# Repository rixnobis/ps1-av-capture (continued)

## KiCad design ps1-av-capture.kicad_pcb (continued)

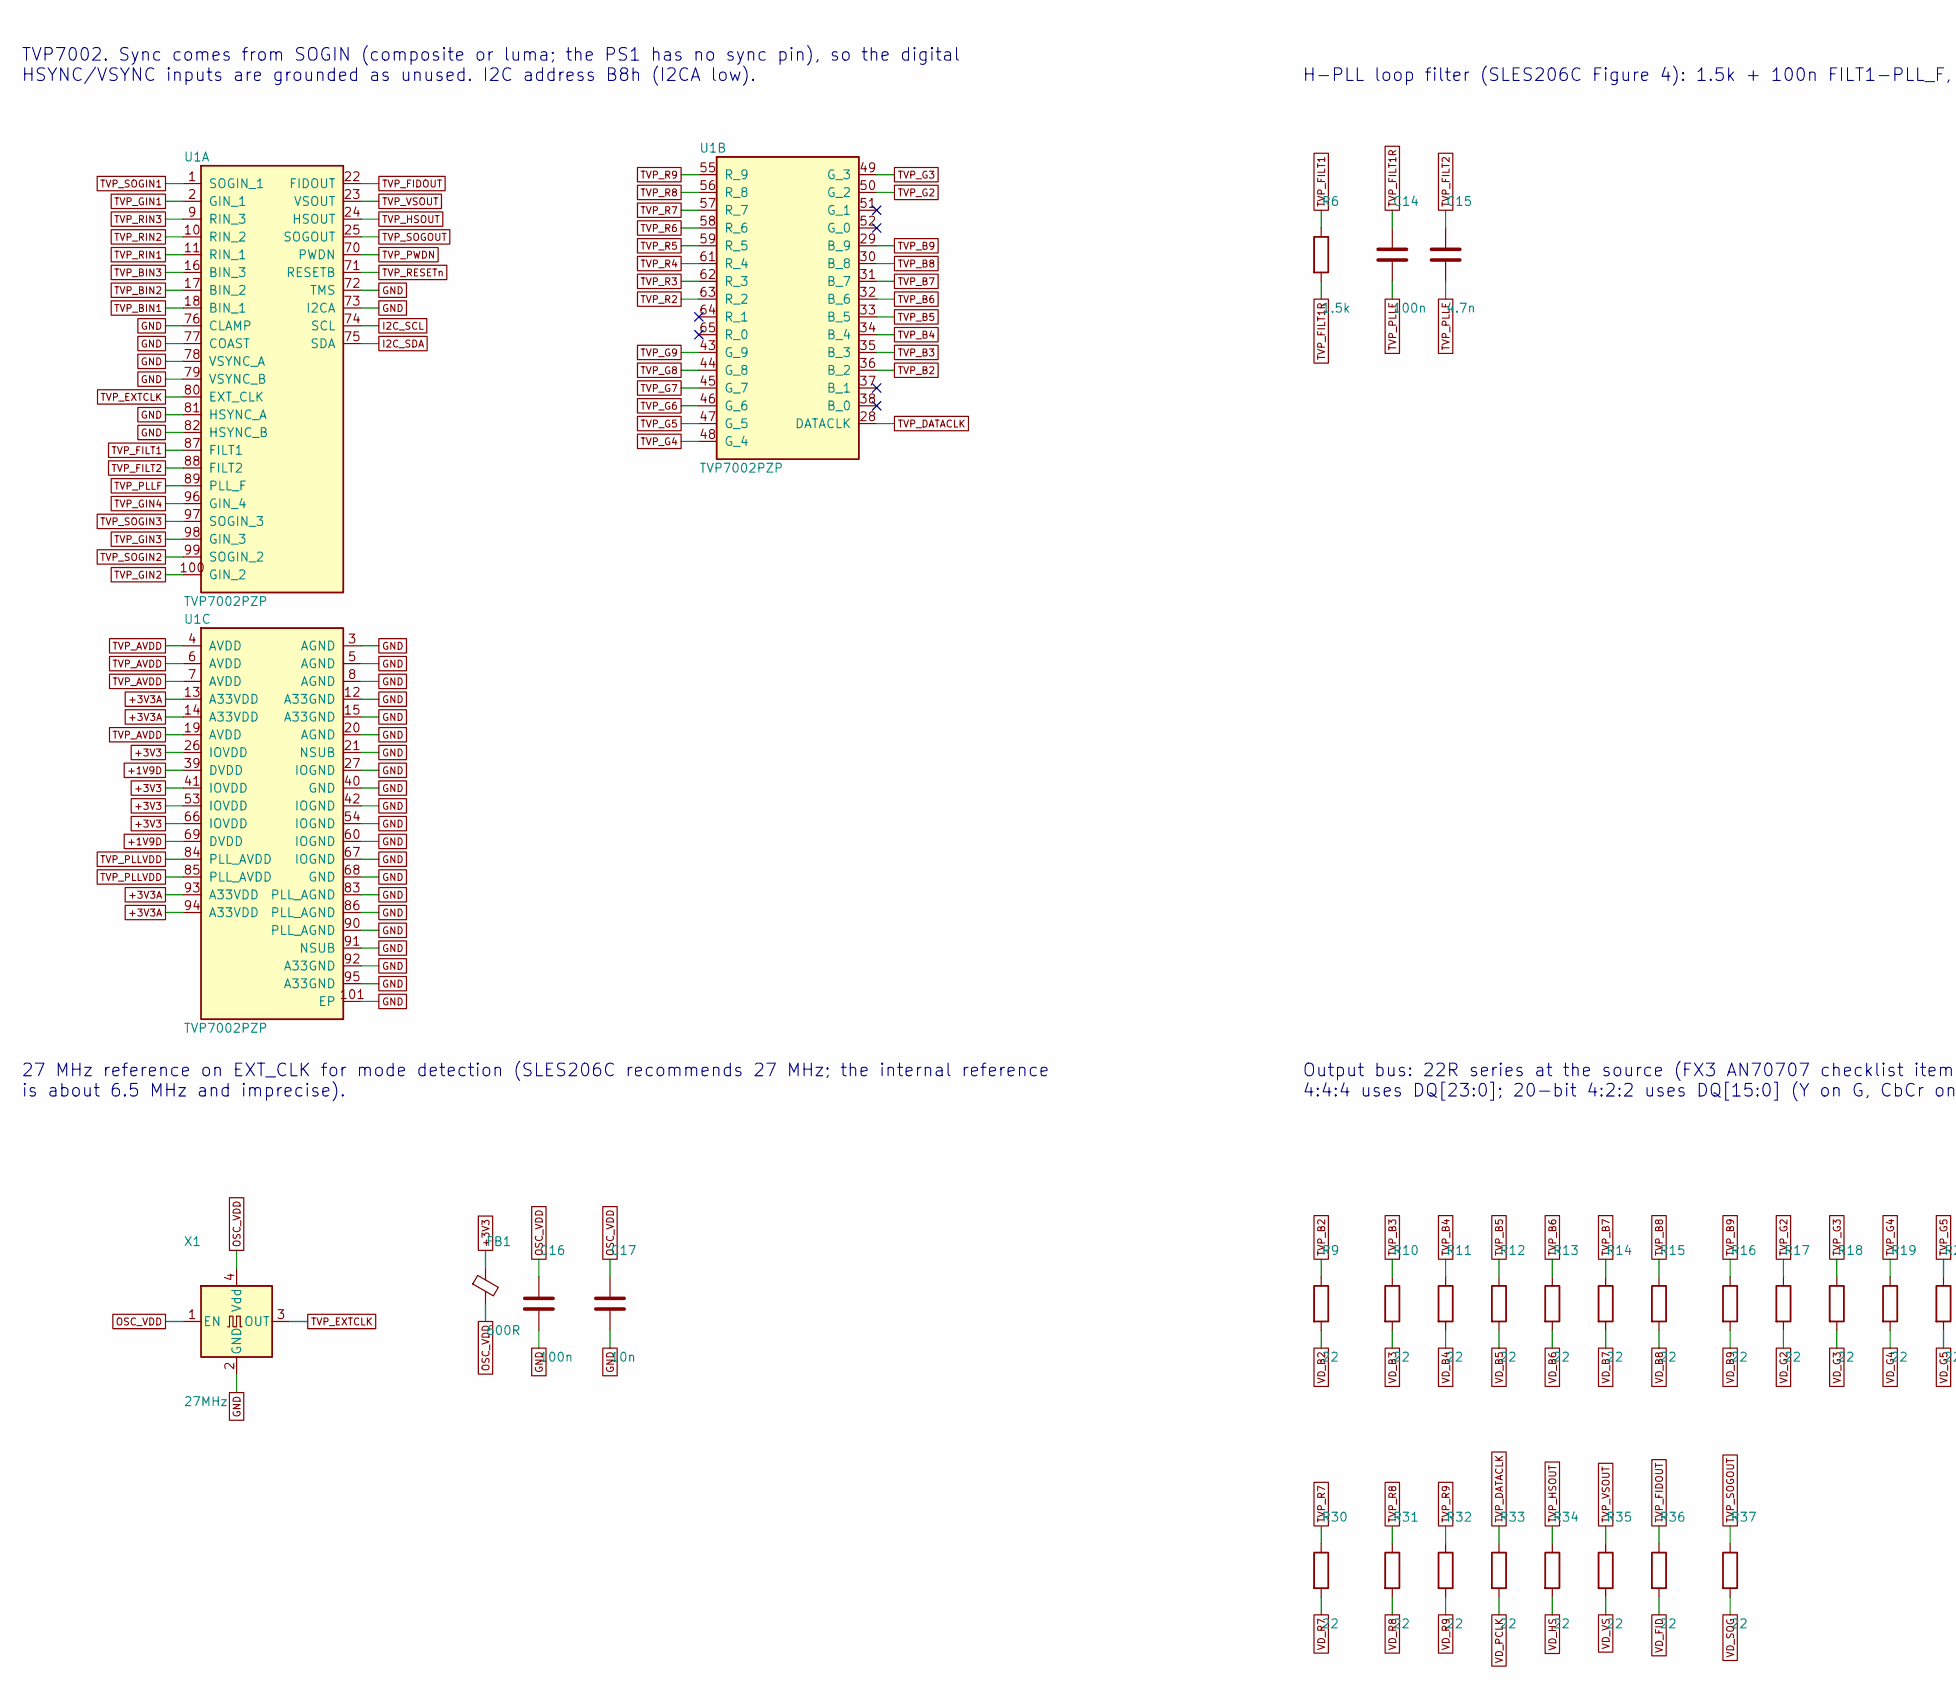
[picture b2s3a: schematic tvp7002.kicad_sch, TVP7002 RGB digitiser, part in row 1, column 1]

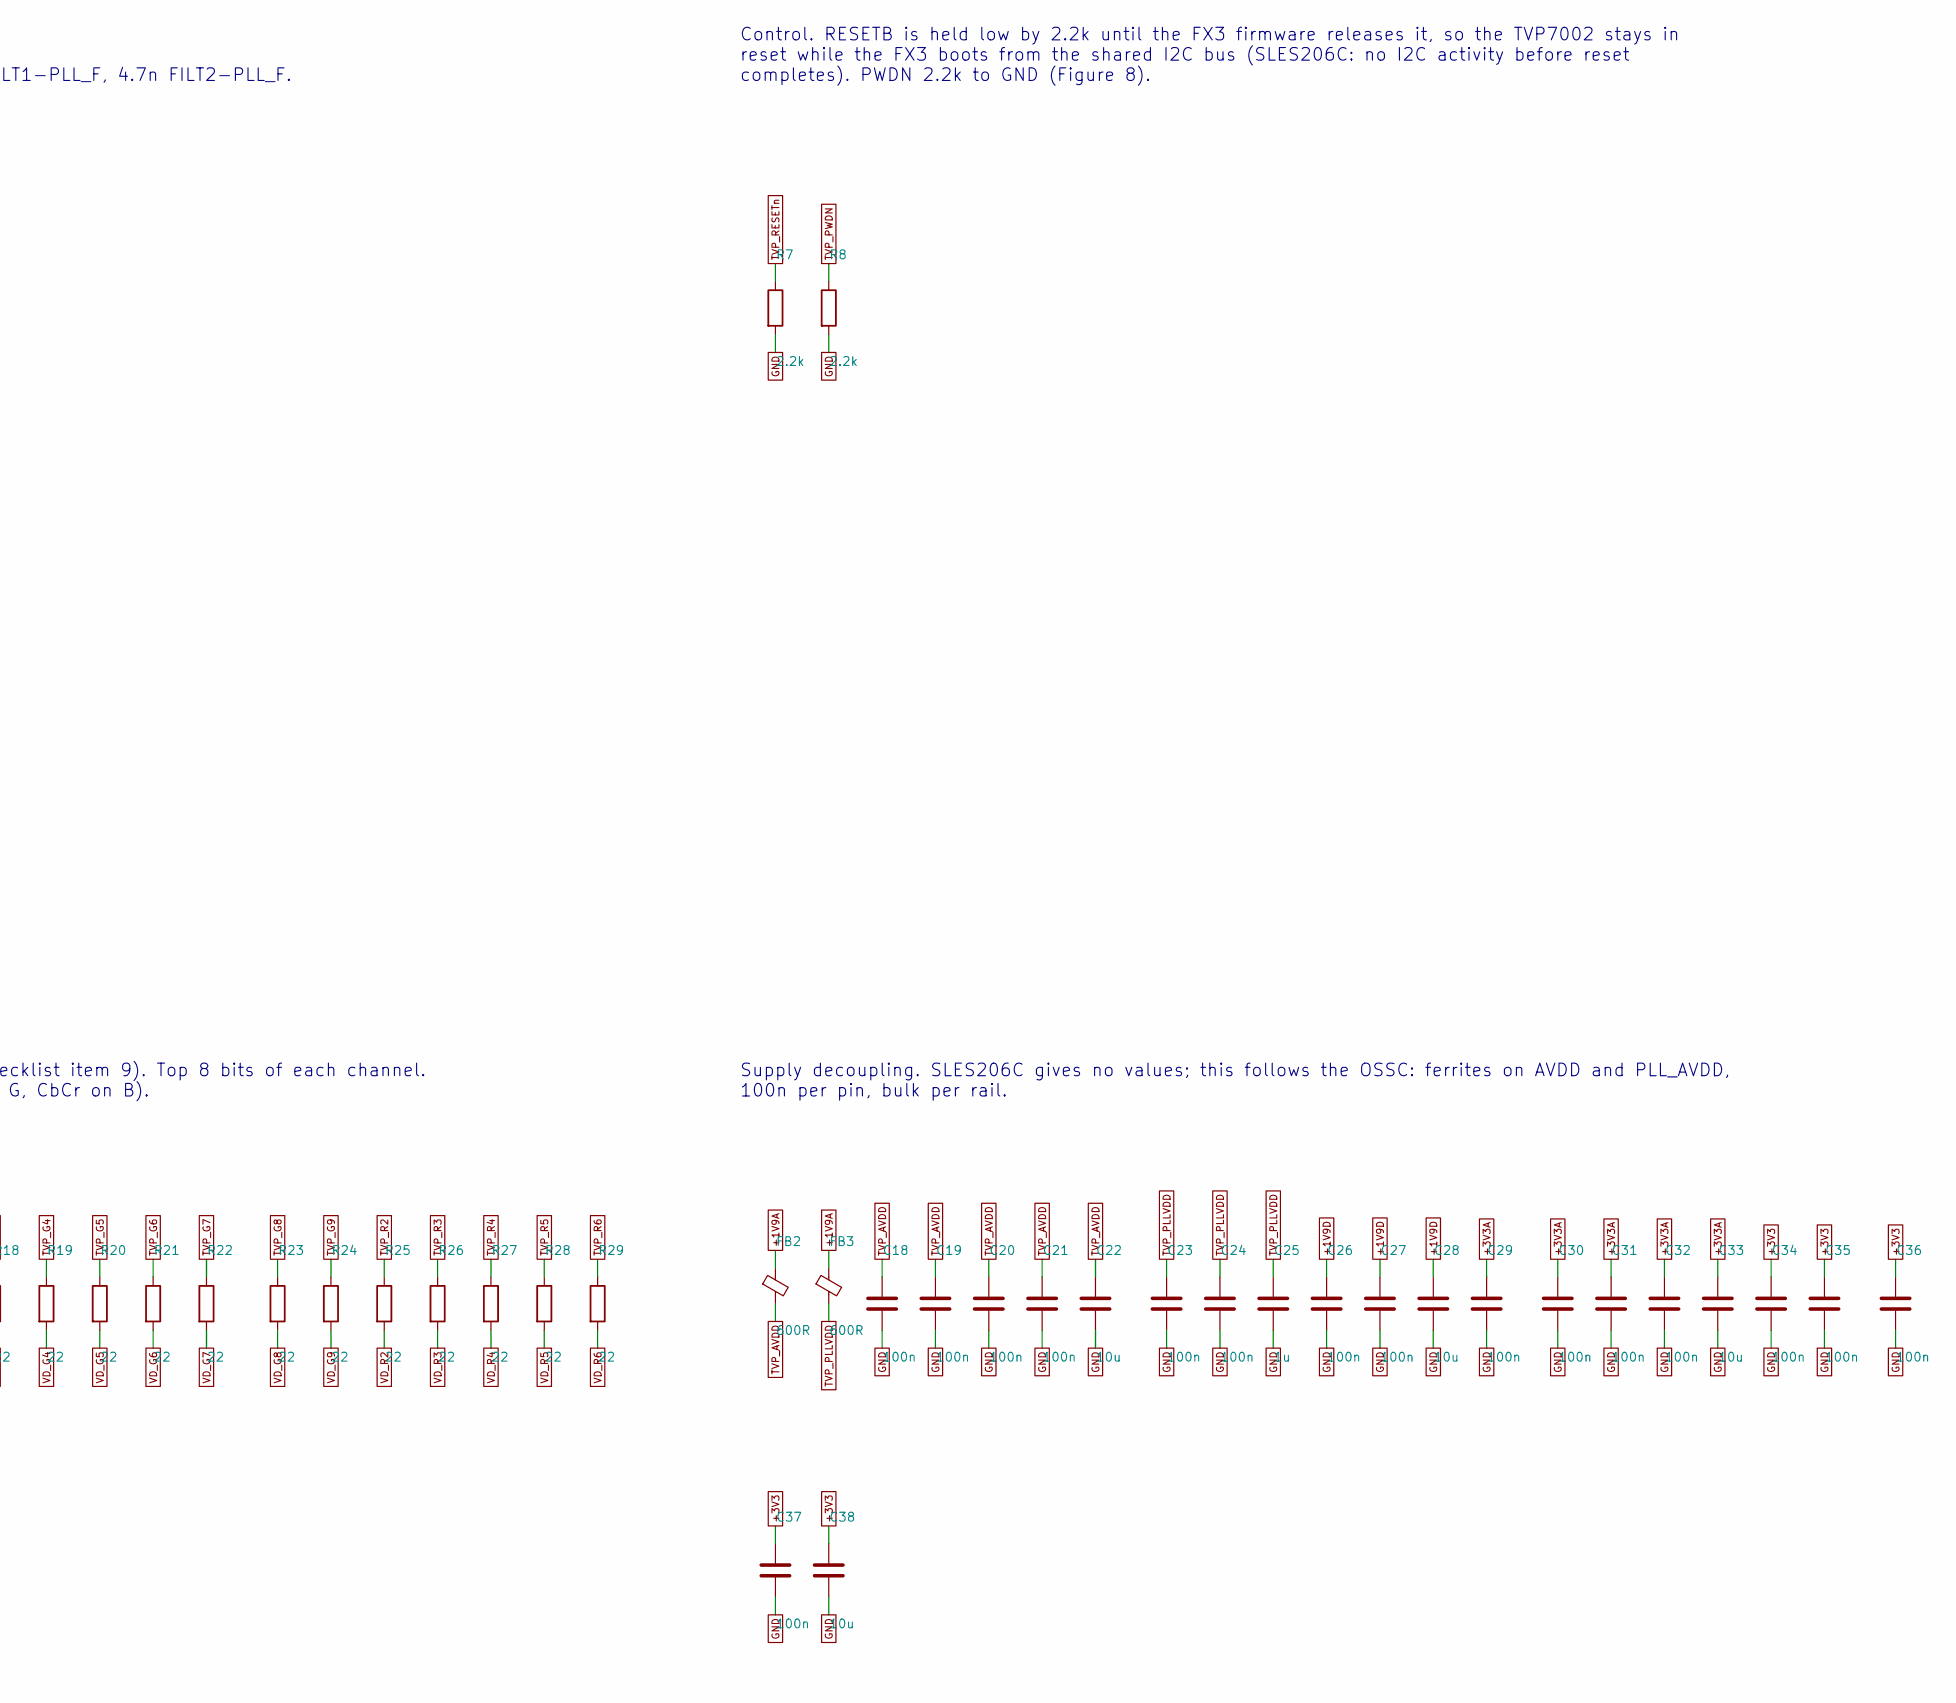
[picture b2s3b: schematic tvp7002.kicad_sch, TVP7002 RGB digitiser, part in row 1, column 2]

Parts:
C14, C16, C18, C19, C20, C21, C23, C24, C26, C27, C29, C30, C31, C32, C34, C35, C36, C37: 100n; C_0402_1005Metric; LCSC C1525
C15: 4.7n; C_0402_1005Metric; LCSC C1538
C17: 10n; C_0402_1005Metric; LCSC C15195
C22, C28, C33, C38: 10u; C_0603_1608Metric; LCSC C19702
C25: 1u; C_0402_1005Metric; LCSC C52923
FB1, FB2, FB3: 600R; L_0603_1608Metric; LCSC C108301
R6: 1.5k; R_0402_1005Metric; LCSC C25867
R7, R8: 2.2k; R_0402_1005Metric; LCSC C25879
R9, R10, R11, R12, R13, R14, R15, R16, R17, R18, R19, R20, R21, R22, R23, R24, R25, R26, R27, R28, R29, R30, R31, R32, R33, R34, R35, R36, R37: 22; R_0402_1005Metric; LCSC C25092
U1: TVP7002PZP; HTQFP-100_L14.0-W14.0-P0.50-LS16.0-BL-EP6.2; LCSC C3824085
X1: 27MHz; Oscillator_SMD_Abracon_ASE-4Pin_3.2x2.5mm; LCSC C725995

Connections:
+1V9A: FB2.1, FB3.1; also elsewhere on the board
+1V9D: C26.1, C27.1, C28.1, U1.39 (DVDD), U1.69 (DVDD); also elsewhere on the board
+3V3: C34.1, C35.1, C36.1, C37.1, C38.1, FB1.1, U1.26 (IOVDD), U1.41 (IOVDD), U1.53 (IOVDD), U1.66 (IOVDD); also elsewhere on the board
+3V3A: C29.1, C30.1, C31.1, C32.1, C33.1, U1.13 (A33VDD), U1.14 (A33VDD), U1.93 (A33VDD), U1.94 (A33VDD); also elsewhere on the board
GND: C16.2, C17.2, C18.2, C19.2, C20.2, C21.2, C22.2, C23.2, C24.2, C25.2, C26.2, C27.2, C28.2, C29.2, C30.2, C31.2, C32.2, C33.2, C34.2, C35.2, C36.2, C37.2, C38.2, R7.2, R8.2, U1.3 (AGND), U1.5 (AGND), U1.8 (AGND), U1.12 (A33GND), U1.15 (A33GND), U1.20 (AGND), U1.21 (NSUB), U1.27 (IOGND), U1.40 (GND), U1.42 (IOGND), U1.54 (IOGND), U1.60 (IOGND), U1.67 (IOGND), U1.68 (GND), U1.72 (TMS), U1.73 (I2CA), U1.76 (CLAMP), U1.77 (COAST), U1.78 (VSYNC_A), U1.79 (VSYNC_B), U1.81 (HSYNC_A), U1.82 (HSYNC_B), U1.83 (PLL_AGND), U1.86 (PLL_AGND), U1.90 (PLL_AGND), U1.91 (NSUB), U1.92 (A33GND), U1.95 (A33GND), U1.101 (EP), X1.2 (GND); also elsewhere on the board
I2C_SCL: U1.74 (SCL); also elsewhere on the board
I2C_SDA: U1.75 (SDA); also elsewhere on the board
OSC_VDD: C16.1, C17.1, FB1.2, X1.1 (EN), X1.4 (Vdd)
TVP_AVDD: C18.1, C19.1, C20.1, C21.1, C22.1, FB2.2, U1.4 (AVDD), U1.6 (AVDD), U1.7 (AVDD), U1.19 (AVDD)
TVP_B2: R9.1, U1.36 (B_2)
TVP_B3: R10.1, U1.35 (B_3)
TVP_B4: R11.1, U1.34 (B_4)
TVP_B5: R12.1, U1.33 (B_5)
TVP_B6: R13.1, U1.32 (B_6)
TVP_B7: R14.1, U1.31 (B_7)
TVP_B8: R15.1, U1.30 (B_8)
TVP_B9: R16.1, U1.29 (B_9)
TVP_BIN1: U1.18 (BIN_1); also elsewhere on the board
TVP_BIN2: U1.17 (BIN_2); also elsewhere on the board
TVP_BIN3: U1.16 (BIN_3); also elsewhere on the board
TVP_DATACLK: R33.1, U1.28 (DATACLK)
TVP_EXTCLK: U1.80 (EXT_CLK), X1.3 (OUT)
TVP_FIDOUT: R36.1, U1.22 (FIDOUT)
TVP_FILT1: R6.1, U1.87 (FILT1)
TVP_FILT1R: C14.1, R6.2
TVP_FILT2: C15.1, U1.88 (FILT2)
TVP_G2: R17.1, U1.50 (G_2)
TVP_G3: R18.1, U1.49 (G_3)
TVP_G4: R19.1, U1.48 (G_4)
TVP_G5: R20.1, U1.47 (G_5)
TVP_G6: R21.1, U1.46 (G_6)
TVP_G7: R22.1, U1.45 (G_7)
TVP_G8: R23.1, U1.44 (G_8)
TVP_G9: R24.1, U1.43 (G_9)
TVP_GIN1: U1.2 (GIN_1); also elsewhere on the board
TVP_GIN2: U1.100 (GIN_2); also elsewhere on the board
TVP_GIN3: U1.98 (GIN_3); also elsewhere on the board
TVP_GIN4: U1.96 (GIN_4); also elsewhere on the board
TVP_HSOUT: R34.1, U1.24 (HSOUT)
TVP_PLLF: C14.2, C15.2, U1.89 (PLL_F)
TVP_PLLVDD: C23.1, C24.1, C25.1, FB3.2, U1.84 (PLL_AVDD), U1.85 (PLL_AVDD)
TVP_PWDN: R8.1, U1.70 (PWDN)
TVP_R2: R25.1, U1.63 (R_2)
TVP_R3: R26.1, U1.62 (R_3)
TVP_R4: R27.1, U1.61 (R_4)
TVP_R5: R28.1, U1.59 (R_5)
TVP_R6: R29.1, U1.58 (R_6)
TVP_R7: R30.1, U1.57 (R_7)
TVP_R8: R31.1, U1.56 (R_8)
TVP_R9: R32.1, U1.55 (R_9)
TVP_RESETn: R7.1, U1.71 (RESETB); also elsewhere on the board
TVP_RIN1: U1.11 (RIN_1); also elsewhere on the board
TVP_RIN2: U1.10 (RIN_2); also elsewhere on the board
TVP_RIN3: U1.9 (RIN_3); also elsewhere on the board
TVP_SOGIN1: U1.1 (SOGIN_1); also elsewhere on the board
TVP_SOGIN2: U1.99 (SOGIN_2); also elsewhere on the board
TVP_SOGIN3: U1.97 (SOGIN_3); also elsewhere on the board
TVP_SOGOUT: R37.1, U1.25 (SOGOUT)
TVP_VSOUT: R35.1, U1.23 (VSOUT)
VD_B2: R9.2; also elsewhere on the board
VD_B3: R10.2; also elsewhere on the board
VD_B4: R11.2; also elsewhere on the board
VD_B5: R12.2; also elsewhere on the board
VD_B6: R13.2; also elsewhere on the board
VD_B7: R14.2; also elsewhere on the board
VD_B8: R15.2; also elsewhere on the board
VD_B9: R16.2; also elsewhere on the board
VD_FID: R36.2; also elsewhere on the board
VD_G2: R17.2; also elsewhere on the board
VD_G3: R18.2; also elsewhere on the board
VD_G4: R19.2; also elsewhere on the board
VD_G5: R20.2; also elsewhere on the board
VD_G6: R21.2; also elsewhere on the board
VD_G7: R22.2; also elsewhere on the board
VD_G8: R23.2; also elsewhere on the board
VD_G9: R24.2; also elsewhere on the board
VD_HS: R34.2; also elsewhere on the board
VD_PCLK: R33.2; also elsewhere on the board
VD_R2: R25.2; also elsewhere on the board
VD_R3: R26.2; also elsewhere on the board
VD_R4: R27.2; also elsewhere on the board
VD_R5: R28.2; also elsewhere on the board
VD_R6: R29.2; also elsewhere on the board
VD_R7: R30.2; also elsewhere on the board
VD_R8: R31.2; also elsewhere on the board
VD_R9: R32.2; also elsewhere on the board
VD_SOG: R37.2; also elsewhere on the board
VD_VS: R35.2; also elsewhere on the board

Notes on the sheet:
TVP7002. Sync comes from SOGIN (composite or luma; the PS1 has no sync pin), so the digital HSYNC/VSYNC inputs are grounded as unused. I2C address B8h (I2CA low).
H-PLL loop filter (SLES206C Figure 4): 1.5k + 100n FILT1-PLL_F, 4.7n FILT2-PLL_F.
Control. RESETB is held low by 2.2k until the FX3 firmware releases it, so the TVP7002 stays in reset while the FX3 boots from the shared I2C bus (SLES206C: no I2C activity before reset completes). PWDN 2.2k to GND (Figure 8).
27 MHz reference on EXT_CLK for mode detection (SLES206C recommends 27 MHz; the internal reference is about 6.5 MHz and imprecise).
Output bus: 22R series at the source (FX3 AN70707 checklist item 9). Top 8 bits of each channel. 4:4:4 uses DQ[23:0]; 20-bit 4:2:2 uses DQ[15:0] (Y on G, CbCr on B).
Supply decoupling. SLES206C gives no values; this follows the OSSC: ferrites on AVDD and PLL_AVDD, 100n per pin, bulk per rail.

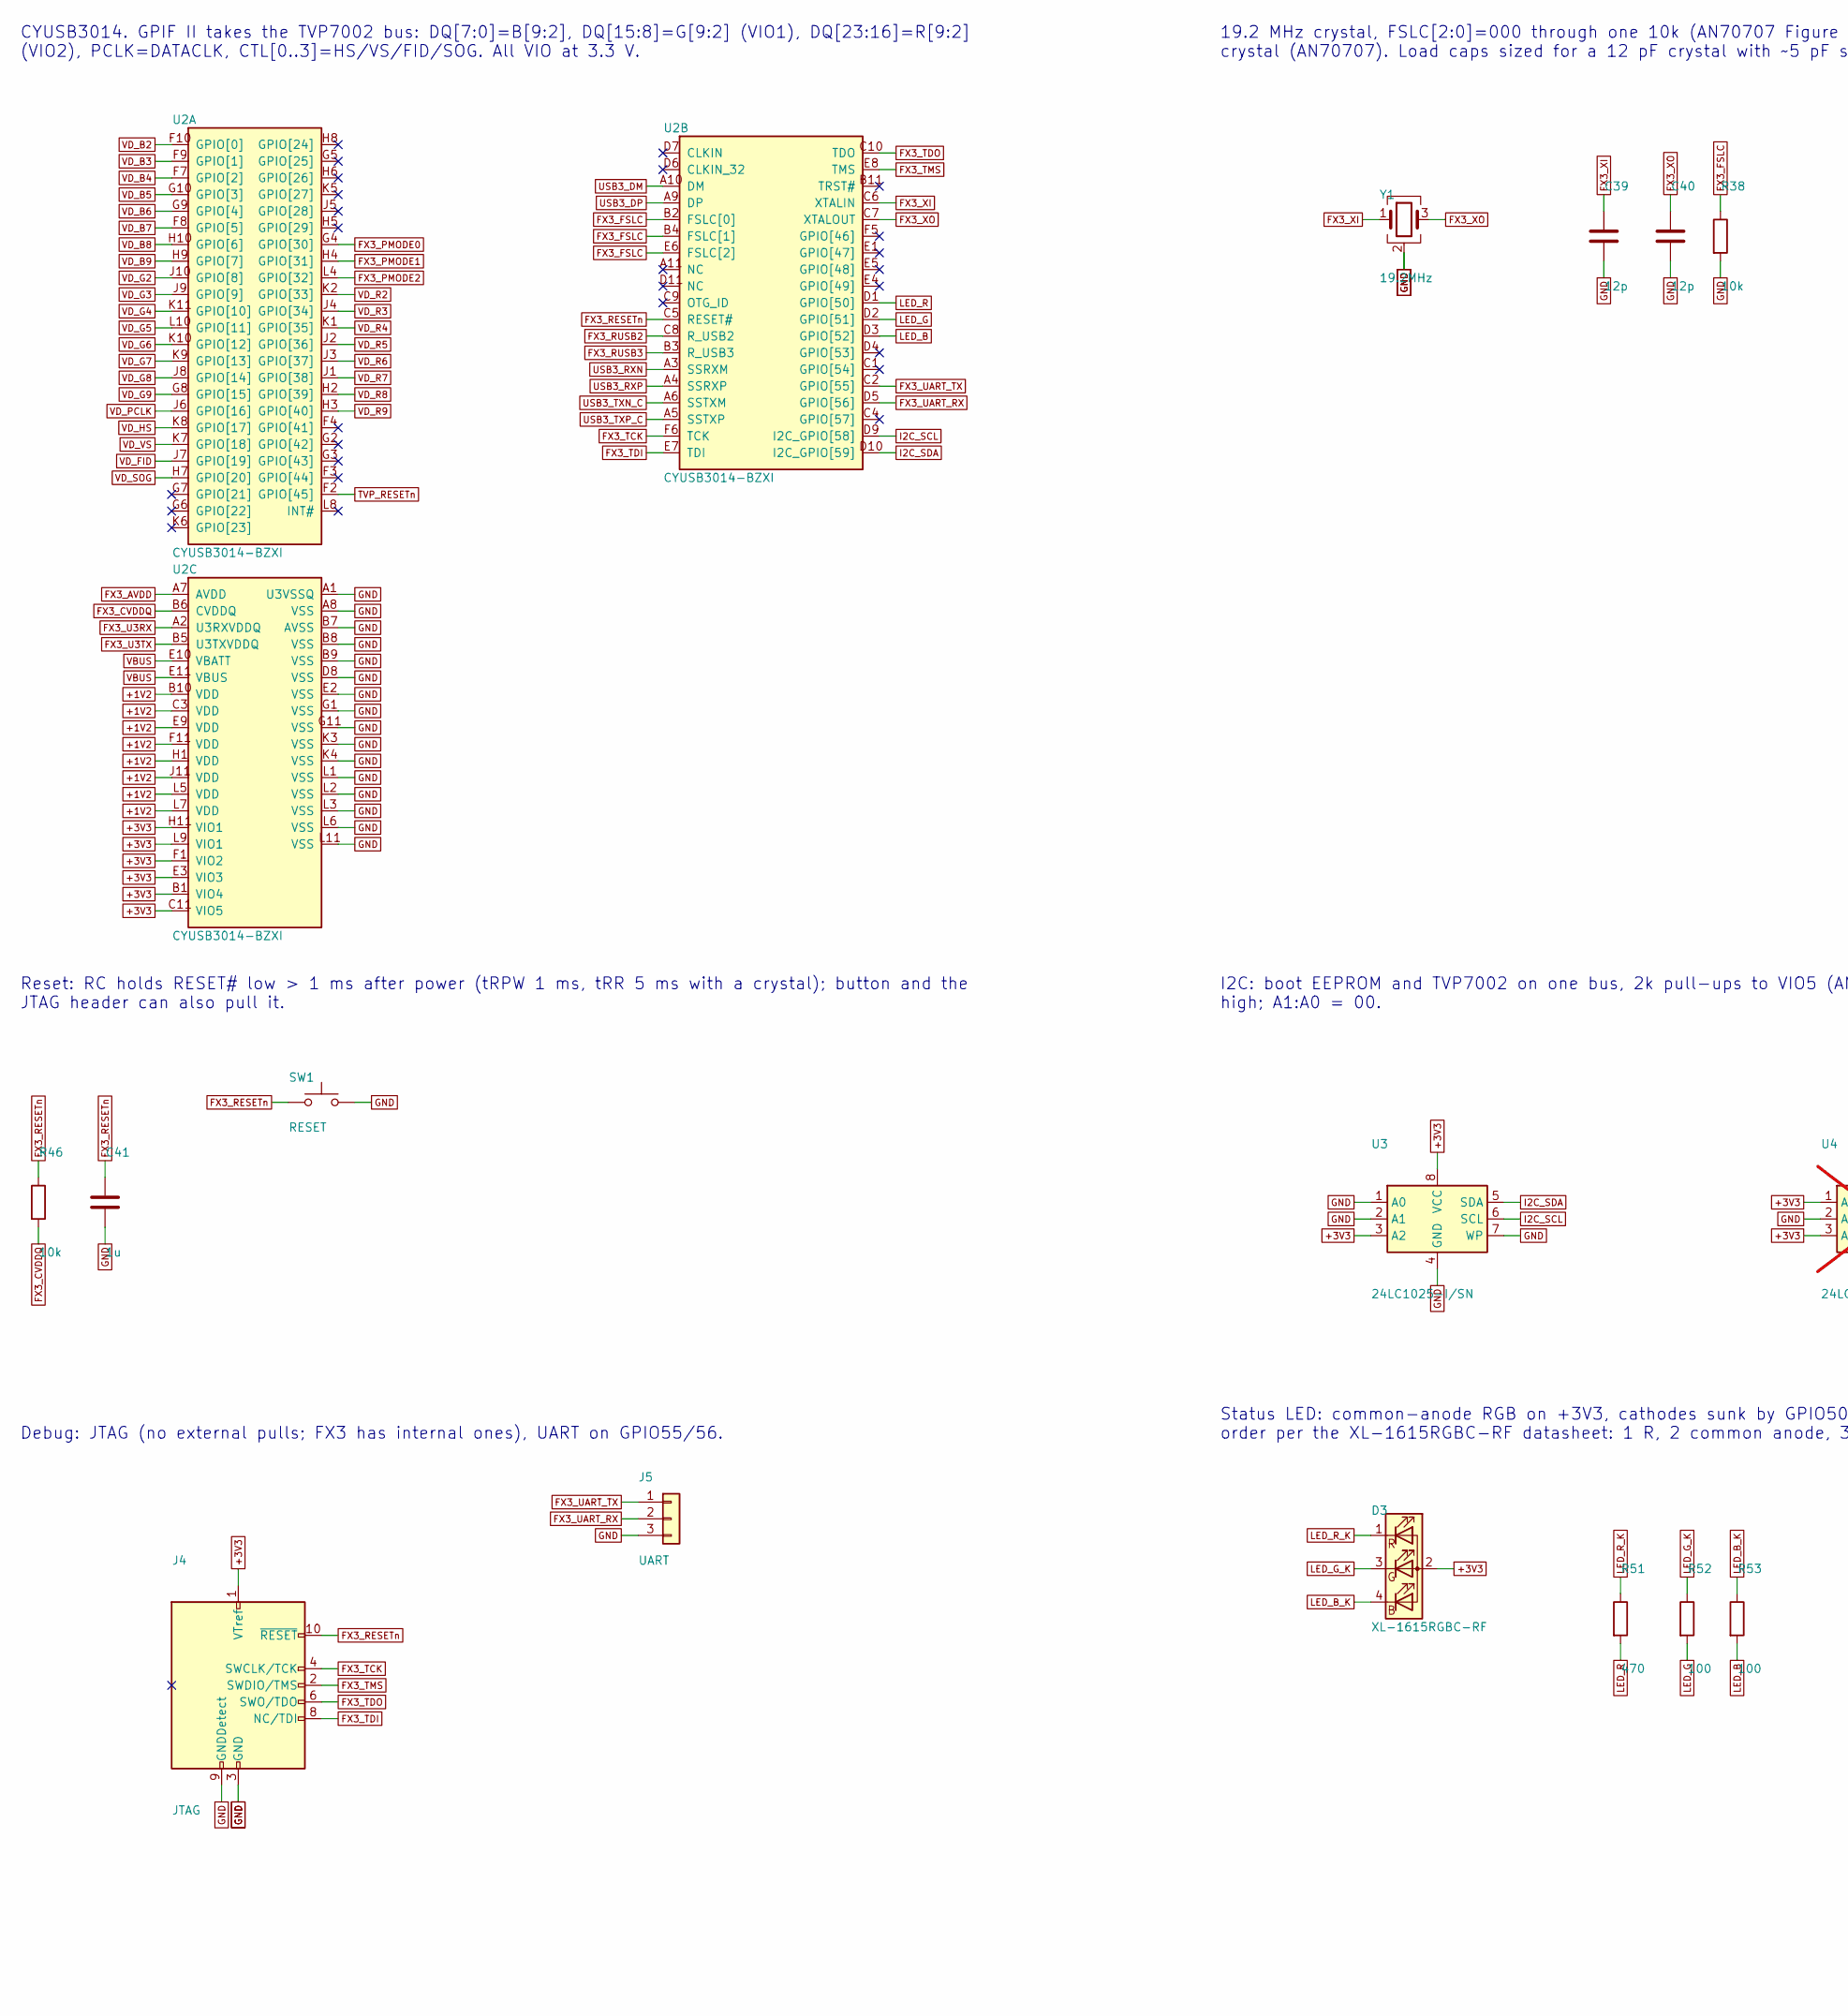
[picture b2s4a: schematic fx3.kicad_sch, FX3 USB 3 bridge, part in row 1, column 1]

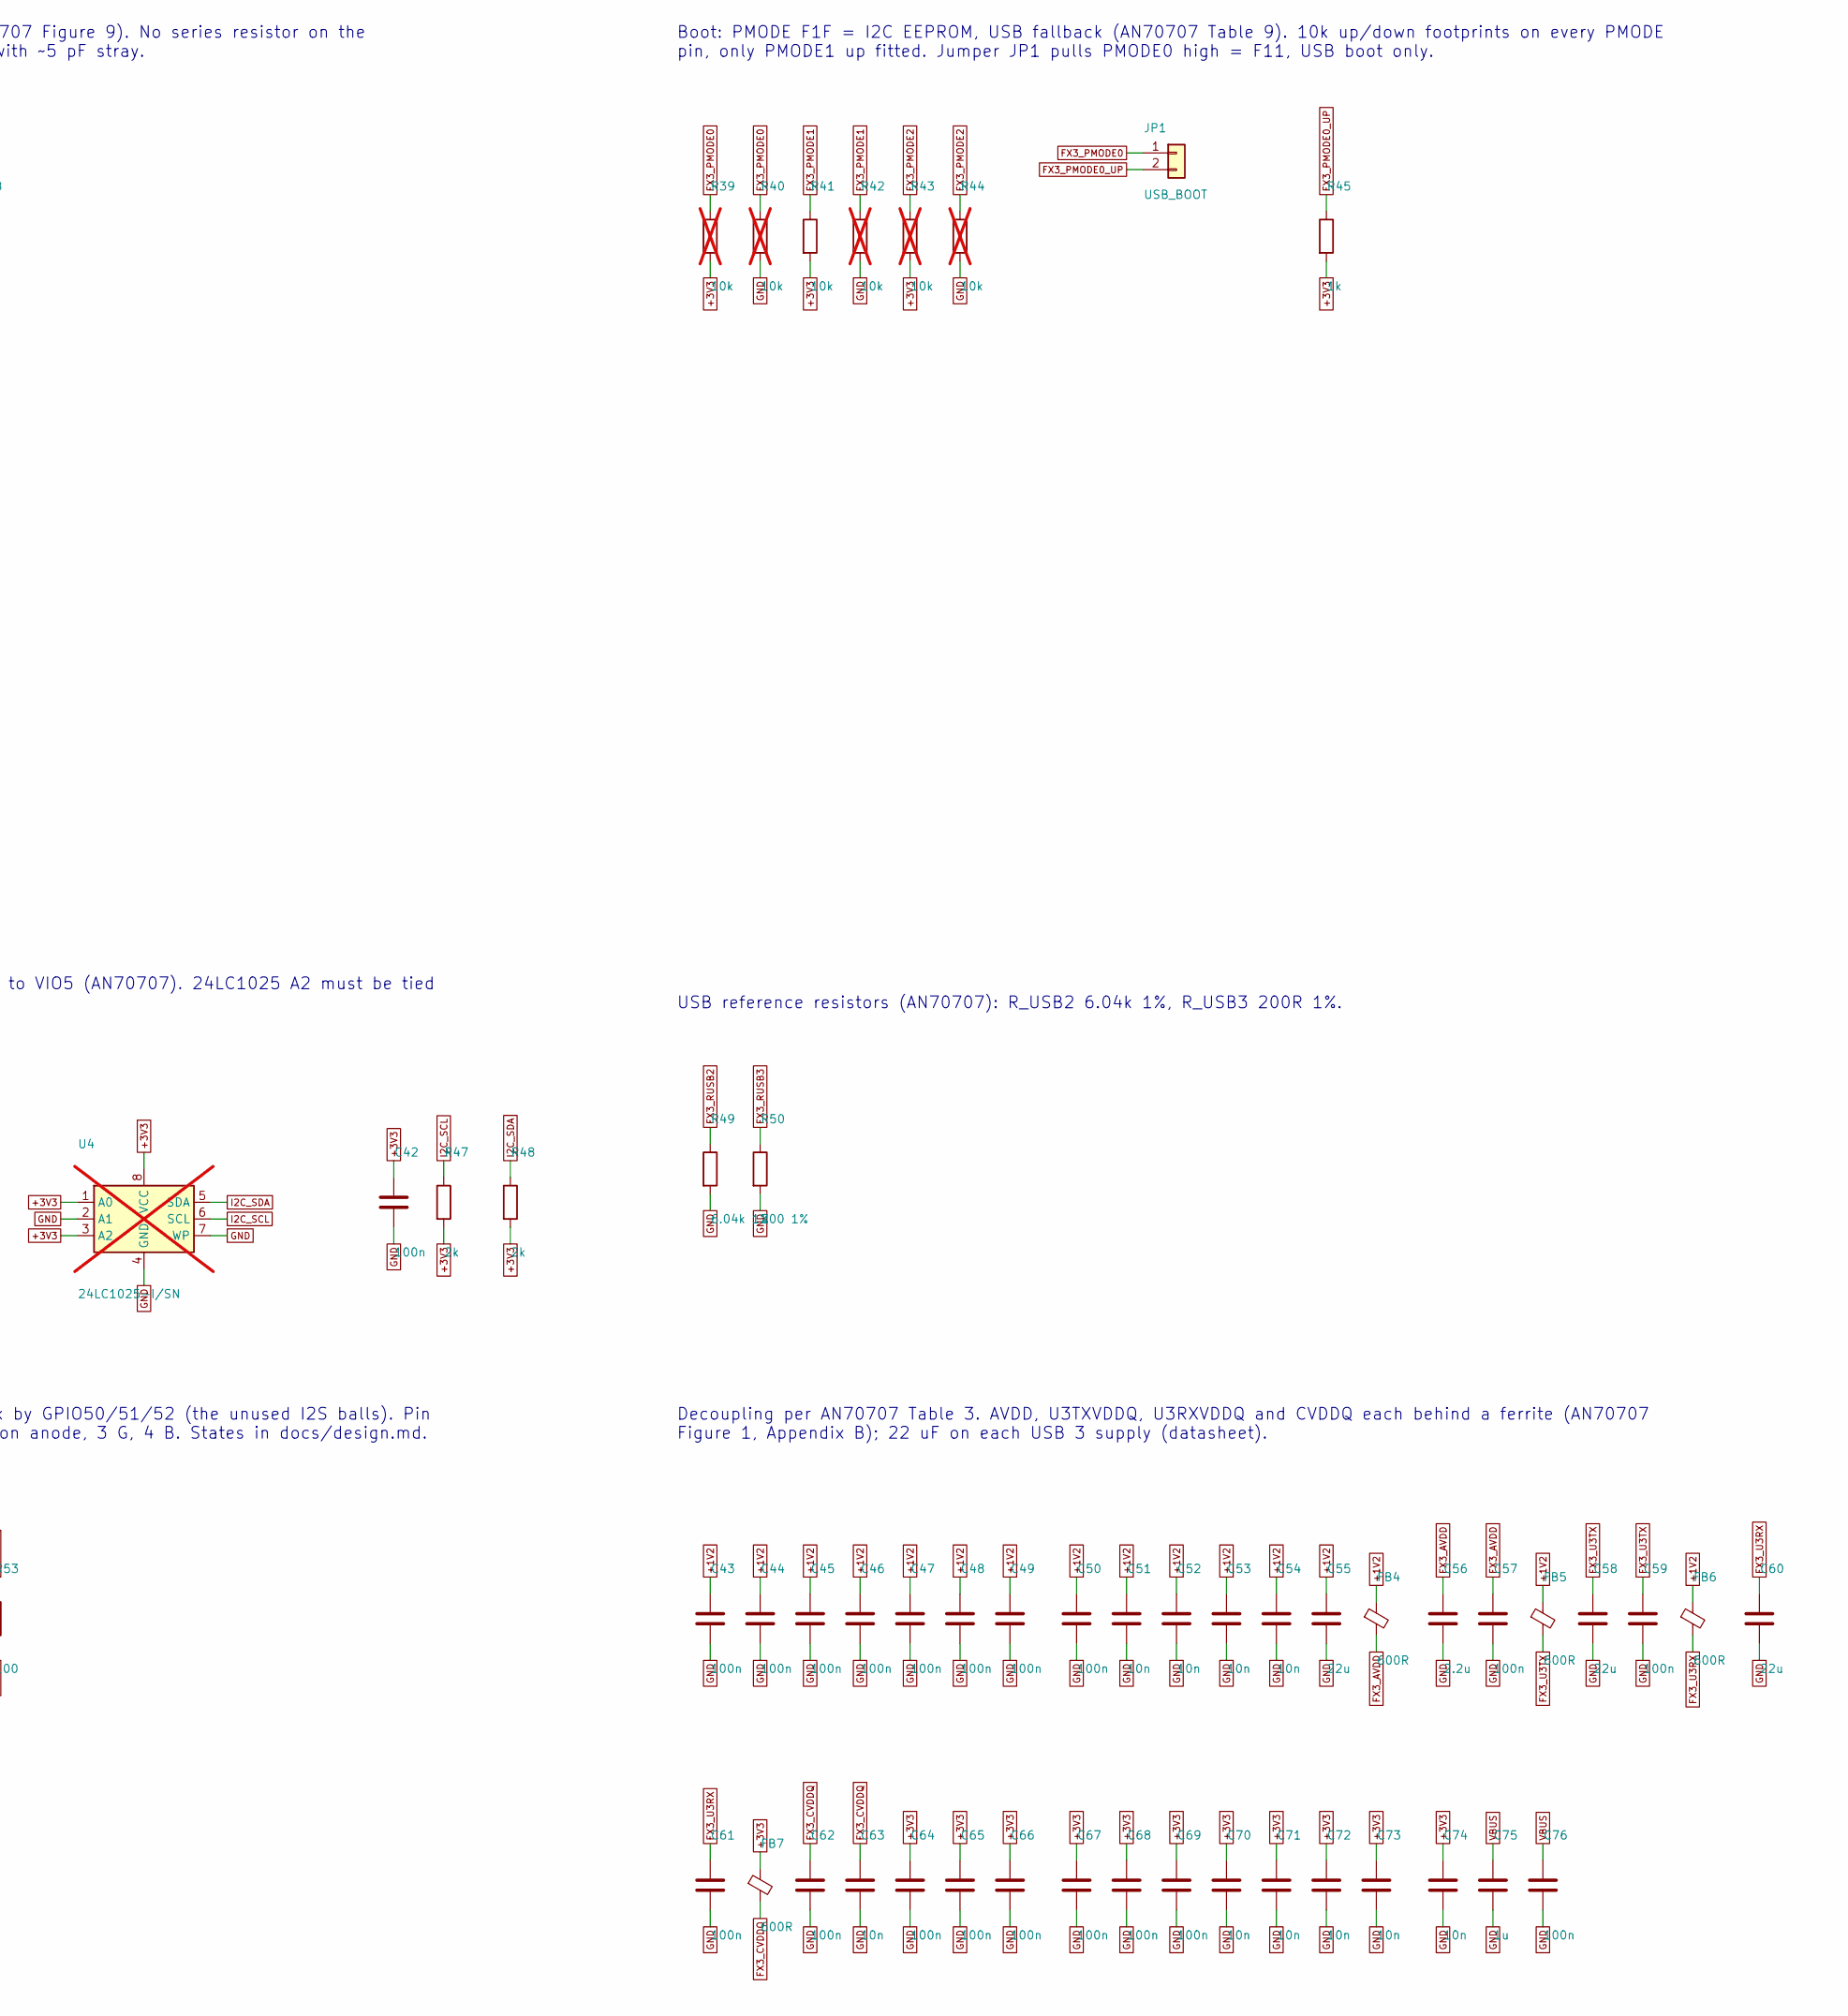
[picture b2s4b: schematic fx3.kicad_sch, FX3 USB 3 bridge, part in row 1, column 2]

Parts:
C39, C40: 12p; C_0402_1005Metric; LCSC C1547
C41, C75: 1u; C_0402_1005Metric; LCSC C52923
C42, C43, C44, C45, C46, C47, C48, C49, C50, C57, C59, C61, C62, C64, C65, C66, C67, C68, C69, C76: 100n; C_0402_1005Metric; LCSC C1525
C51, C52, C53, C54, C63, C70, C71, C72, C73, C74: 10n; C_0402_1005Metric; LCSC C15195
C55, C58, C60: 22u; C_0805_2012Metric; LCSC C45783
C56: 2.2u; C_0603_1608Metric; LCSC C23630
D3: XL-1615RGBC-RF; LED-ARRAY-SMD_4P-L1.6-W1.5-BR_XL-1615RGBC-RF; LCSC C965840
FB4, FB5, FB6, FB7: 600R; L_0603_1608Metric; LCSC C108301
J4: JTAG; PinHeader_2x05_P1.27mm_Vertical_SMD
J5: UART; PinHeader_1x03_P2.54mm_Vertical
JP1: USB_BOOT; PinHeader_1x02_P2.54mm_Vertical
R38, R41, R46: 10k; R_0402_1005Metric; LCSC C25744
R39, R40, R42, R43, R44: 10k; R_0402_1005Metric; LCSC C25744; not fitted
R45: 1k; R_0402_1005Metric; LCSC C11702
R47, R48: 2k; R_0402_1005Metric; LCSC C4109
R49: 6.04k 1%; R_0402_1005Metric; LCSC C97819
R50: 200 1%; R_0402_1005Metric; LCSC C25087
R51: 470; R_0402_1005Metric; LCSC C25117
R52, R53: 100; R_0402_1005Metric; LCSC C25076
SW1: RESET; SW_SPST_TL3342; LCSC C318884
U2: CYUSB3014-BZXI; BGA-121_L10.0-W10.0-R11-C11-P0.80-TL; LCSC C57294
U3: 24LC1025-I/SN; SOIC-8_3.9x4.9mm_P1.27mm; LCSC C615697
U4: 24LC1025-I/SN; SOIC-8_3.9x4.9mm_P1.27mm; LCSC C615697; not fitted
Y1: 19.2MHz; Crystal_SMD_3225-4Pin_3.2x2.5mm; LCSC C411225

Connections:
+1V2: C43.1, C44.1, C45.1, C46.1, C47.1, C48.1, C49.1, C50.1, C51.1, C52.1, C53.1, C54.1, C55.1, FB4.1, FB5.1, FB6.1, U2.B10 (VDD), U2.C3 (VDD), U2.E9 (VDD), U2.F11 (VDD), U2.H1 (VDD), U2.J11 (VDD), U2.L5 (VDD), U2.L7 (VDD); also elsewhere on the board
+3V3: C42.1, C64.1, C65.1, C66.1, C67.1, C68.1, C69.1, C70.1, C71.1, C72.1, C73.1, C74.1, D3.2 (A), FB7.1, J4.1 (VTref), R39.2, R41.2, R43.2, R45.2, R47.2, R48.2, U2.B1 (VIO4), U2.C11 (VIO5), U2.E3 (VIO3), U2.F1 (VIO2), U2.H11 (VIO1), U2.L9 (VIO1), U3.3 (A2), U3.8 (VCC), U4.1 (A0), U4.3 (A2), U4.8 (VCC); also elsewhere on the board
FX3_AVDD: C56.1, C57.1, FB4.2, U2.A7 (AVDD)
FX3_CVDDQ: C62.1, C63.1, FB7.2, R46.2, U2.B6 (CVDDQ)
FX3_FSLC: R38.1, U2.B2 (FSLC[0]), U2.B4 (FSLC[1]), U2.E6 (FSLC[2])
FX3_PMODE0: JP1.1, R39.1, R40.1, U2.G4 (GPIO[30])
FX3_PMODE0_UP: JP1.2, R45.1
FX3_PMODE1: R41.1, R42.1, U2.H4 (GPIO[31])
FX3_PMODE2: R43.1, R44.1, U2.L4 (GPIO[32])
FX3_RESETn: C41.1, J4.10 (~RESET), R46.1, SW1.1, U2.C5 (RESET#)
FX3_RUSB2: R49.1, U2.C8 (R_USB2)
FX3_RUSB3: R50.1, U2.B3 (R_USB3)
FX3_TCK: J4.4 (SWCLK/TCK), U2.F6 (TCK)
FX3_TDI: J4.8 (NC/TDI), U2.E7 (TDI)
FX3_TDO: J4.6 (SWO/TDO), U2.C10 (TDO)
FX3_TMS: J4.2 (SWDIO/TMS), U2.E8 (TMS)
FX3_U3RX: C60.1, C61.1, FB6.2, U2.A2 (U3RXVDDQ)
FX3_U3TX: C58.1, C59.1, FB5.2, U2.B5 (U3TXVDDQ)
FX3_UART_RX: J5.2, U2.D5 (GPIO[56])
FX3_UART_TX: J5.1, U2.C2 (GPIO[55])
FX3_XI: C39.1, U2.C6 (XTALIN), Y1.1
FX3_XO: C40.1, U2.C7 (XTALOUT), Y1.3
GND: C39.2, C40.2, C41.2, C42.2, C43.2, C44.2, C45.2, C46.2, C47.2, C48.2, C49.2, C50.2, C51.2, C52.2, C53.2, C54.2, C55.2, C56.2, C57.2, C58.2, C59.2, C60.2, C61.2, C62.2, C63.2, C64.2, C65.2, C66.2, C67.2, C68.2, C69.2, C70.2, C71.2, C72.2, C73.2, C74.2, C75.2, C76.2, J4.3 (GND), J4.5 (GND), J4.9 (GNDDetect), J5.3, R38.2, R40.2, R42.2, R44.2, R49.2, R50.2, SW1.2, U2.A1 (U3VSSQ), U2.A8 (VSS), U2.B7 (AVSS), U2.B8 (VSS), U2.B9 (VSS), U2.D8 (VSS), U2.E2 (VSS), U2.G1 (VSS), U2.G11 (VSS), U2.K3 (VSS), U2.K4 (VSS), U2.L1 (VSS), U2.L2 (VSS), U2.L3 (VSS), U2.L6 (VSS), U2.L11 (VSS), U3.1 (A0), U3.2 (A1), U3.4 (GND), U3.7 (WP), U4.2 (A1), U4.4 (GND), U4.7 (WP), Y1.2 (G), Y1.4 (G); also elsewhere on the board
I2C_SCL: R47.1, U2.D9 (I2C_GPIO[58]), U3.6 (SCL), U4.6 (SCL); also elsewhere on the board
I2C_SDA: R48.1, U2.D10 (I2C_GPIO[59]), U3.5 (SDA), U4.5 (SDA); also elsewhere on the board
LED_B: R53.2, U2.D3 (GPIO[52])
LED_B_K: D3.4 (BK), R53.1
LED_G: R52.2, U2.D2 (GPIO[51])
LED_G_K: D3.3 (GK), R52.1
LED_R: R51.2, U2.D1 (GPIO[50])
LED_R_K: D3.1 (RK), R51.1
TVP_RESETn: U2.F2 (GPIO[45]); also elsewhere on the board
USB3_DM: U2.A10 (DM); also elsewhere on the board
USB3_DP: U2.A9 (DP); also elsewhere on the board
USB3_RXN: U2.A3 (SSRXM); also elsewhere on the board
USB3_RXP: U2.A4 (SSRXP); also elsewhere on the board
USB3_TXN_C: U2.A6 (SSTXM); also elsewhere on the board
USB3_TXP_C: U2.A5 (SSTXP); also elsewhere on the board
VBUS: C75.1, C76.1, U2.E10 (VBATT), U2.E11 (VBUS); also elsewhere on the board
VD_B2: U2.F10 (GPIO[0]); also elsewhere on the board
VD_B3: U2.F9 (GPIO[1]); also elsewhere on the board
VD_B4: U2.F7 (GPIO[2]); also elsewhere on the board
VD_B5: U2.G10 (GPIO[3]); also elsewhere on the board
VD_B6: U2.G9 (GPIO[4]); also elsewhere on the board
VD_B7: U2.F8 (GPIO[5]); also elsewhere on the board
VD_B8: U2.H10 (GPIO[6]); also elsewhere on the board
VD_B9: U2.H9 (GPIO[7]); also elsewhere on the board
VD_FID: U2.J7 (GPIO[19]); also elsewhere on the board
VD_G2: U2.J10 (GPIO[8]); also elsewhere on the board
VD_G3: U2.J9 (GPIO[9]); also elsewhere on the board
VD_G4: U2.K11 (GPIO[10]); also elsewhere on the board
VD_G5: U2.L10 (GPIO[11]); also elsewhere on the board
VD_G6: U2.K10 (GPIO[12]); also elsewhere on the board
VD_G7: U2.K9 (GPIO[13]); also elsewhere on the board
VD_G8: U2.J8 (GPIO[14]); also elsewhere on the board
VD_G9: U2.G8 (GPIO[15]); also elsewhere on the board
VD_HS: U2.K8 (GPIO[17]); also elsewhere on the board
VD_PCLK: U2.J6 (GPIO[16]); also elsewhere on the board
VD_R2: U2.K2 (GPIO[33]); also elsewhere on the board
VD_R3: U2.J4 (GPIO[34]); also elsewhere on the board
VD_R4: U2.K1 (GPIO[35]); also elsewhere on the board
VD_R5: U2.J2 (GPIO[36]); also elsewhere on the board
VD_R6: U2.J3 (GPIO[37]); also elsewhere on the board
VD_R7: U2.J1 (GPIO[38]); also elsewhere on the board
VD_R8: U2.H2 (GPIO[39]); also elsewhere on the board
VD_R9: U2.H3 (GPIO[40]); also elsewhere on the board
VD_SOG: U2.H7 (GPIO[20]); also elsewhere on the board
VD_VS: U2.K7 (GPIO[18]); also elsewhere on the board

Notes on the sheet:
CYUSB3014. GPIF II takes the TVP7002 bus: DQ[7:0]=B[9:2], DQ[15:8]=G[9:2] (VIO1), DQ[23:16]=R[9:2] (VIO2), PCLK=DATACLK, CTL[0..3]=HS/VS/FID/SOG. All VIO at 3.3 V.
19.2 MHz crystal, FSLC[2:0]=000 through one 10k (AN70707 Figure 9). No series resistor on the crystal (AN70707). Load caps sized for a 12 pF crystal with ~5 pF stray.
Boot: PMODE F1F = I2C EEPROM, USB fallback (AN70707 Table 9). 10k up/down footprints on every PMODE pin, only PMODE1 up fitted. Jumper JP1 pulls PMODE0 high = F11, USB boot only.
Reset: RC holds RESET# low > 1 ms after power (tRPW 1 ms, tRR 5 ms with a crystal); button and the JTAG header can also pull it.
I2C: boot EEPROM and TVP7002 on one bus, 2k pull-ups to VIO5 (AN70707). 24LC1025 A2 must be tied high; A1:A0 = 00.
USB reference resistors (AN70707): R_USB2 6.04k 1%, R_USB3 200R 1%.
Debug: JTAG (no external pulls; FX3 has internal ones), UART on GPIO55/56.
Status LED: common-anode RGB on +3V3, cathodes sunk by GPIO50/51/52 (the unused I2S balls). Pin order per the XL-1615RGBC-RF datasheet: 1 R, 2 common anode, 3 G, 4 B. States in docs/design.md.
Decoupling per AN70707 Table 3. AVDD, U3TXVDDQ, U3RXVDDQ and CVDDQ each behind a ferrite (AN70707 Figure 1, Appendix B); 22 uF on each USB 3 supply (datasheet).
